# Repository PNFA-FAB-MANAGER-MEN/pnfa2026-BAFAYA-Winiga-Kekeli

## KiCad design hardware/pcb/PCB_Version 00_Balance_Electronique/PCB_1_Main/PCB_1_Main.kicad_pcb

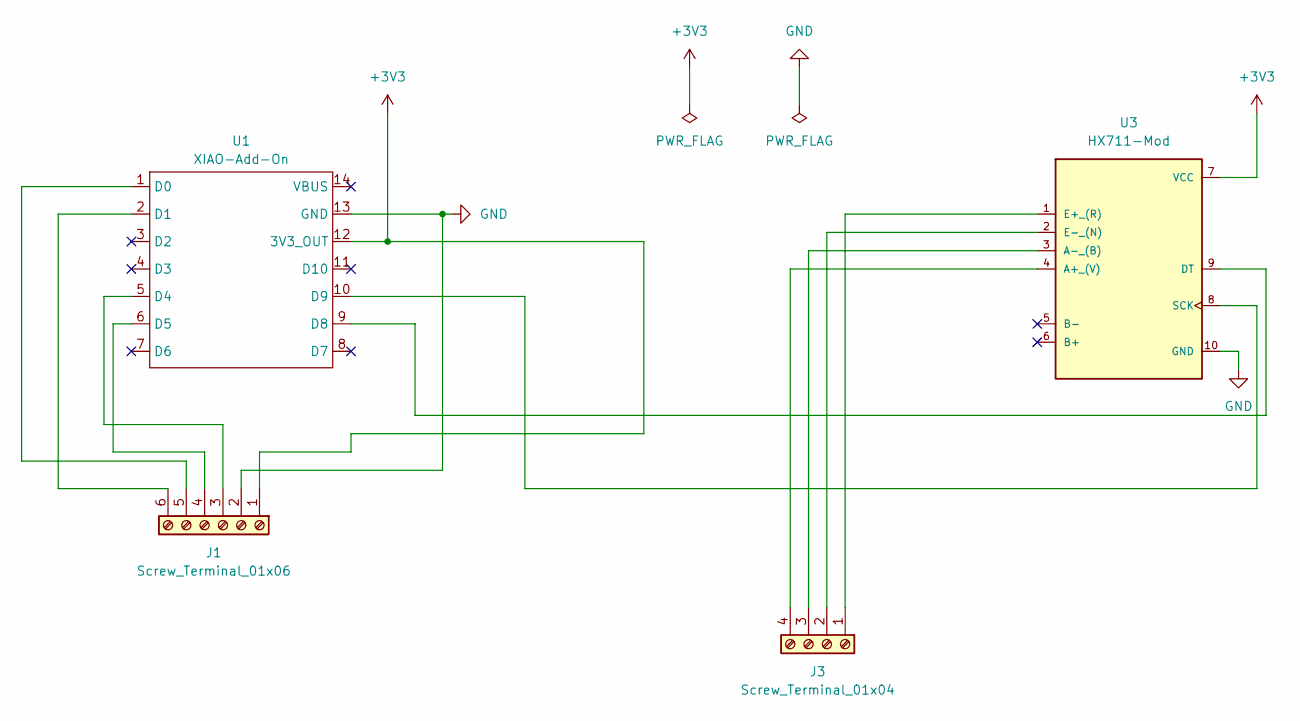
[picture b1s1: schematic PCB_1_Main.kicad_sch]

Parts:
J1: Screw_Terminal_01x06; TerminalBlock_MaiXu_MX126-5.0-06P_1x06_P5.00mm
J3: Screw_Terminal_01x04; TerminalBlock_MaiXu_MX126-5.0-04P_1x04_P5.00mm
U1: XIAO-Add-On; XIAO-14P-Add-On
U3: HX711-Mod; HX711_module

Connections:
+3V3: J1.1, U1.12 (3V3_OUT), U3.7 (VCC)
GND: J1.2, U1.13 (GND), U3.10 (GND)
unnamed: J1.3, U1.5 (D4)
unnamed: J1.4, U1.6 (D5)
unnamed: J1.5, U1.1 (D0)
unnamed: J1.6, U1.2 (D1)
unnamed: J3.1, U3.1 (E+_(R))
unnamed: J3.2, U3.2 (E-_(N))
unnamed: J3.3, U3.3 (A-_(B))
unnamed: J3.4, U3.4 (A+_(V))
unnamed: U1.9 (D8), U3.9 (DT)
unnamed: U1.10 (D9), U3.8 (SCK)

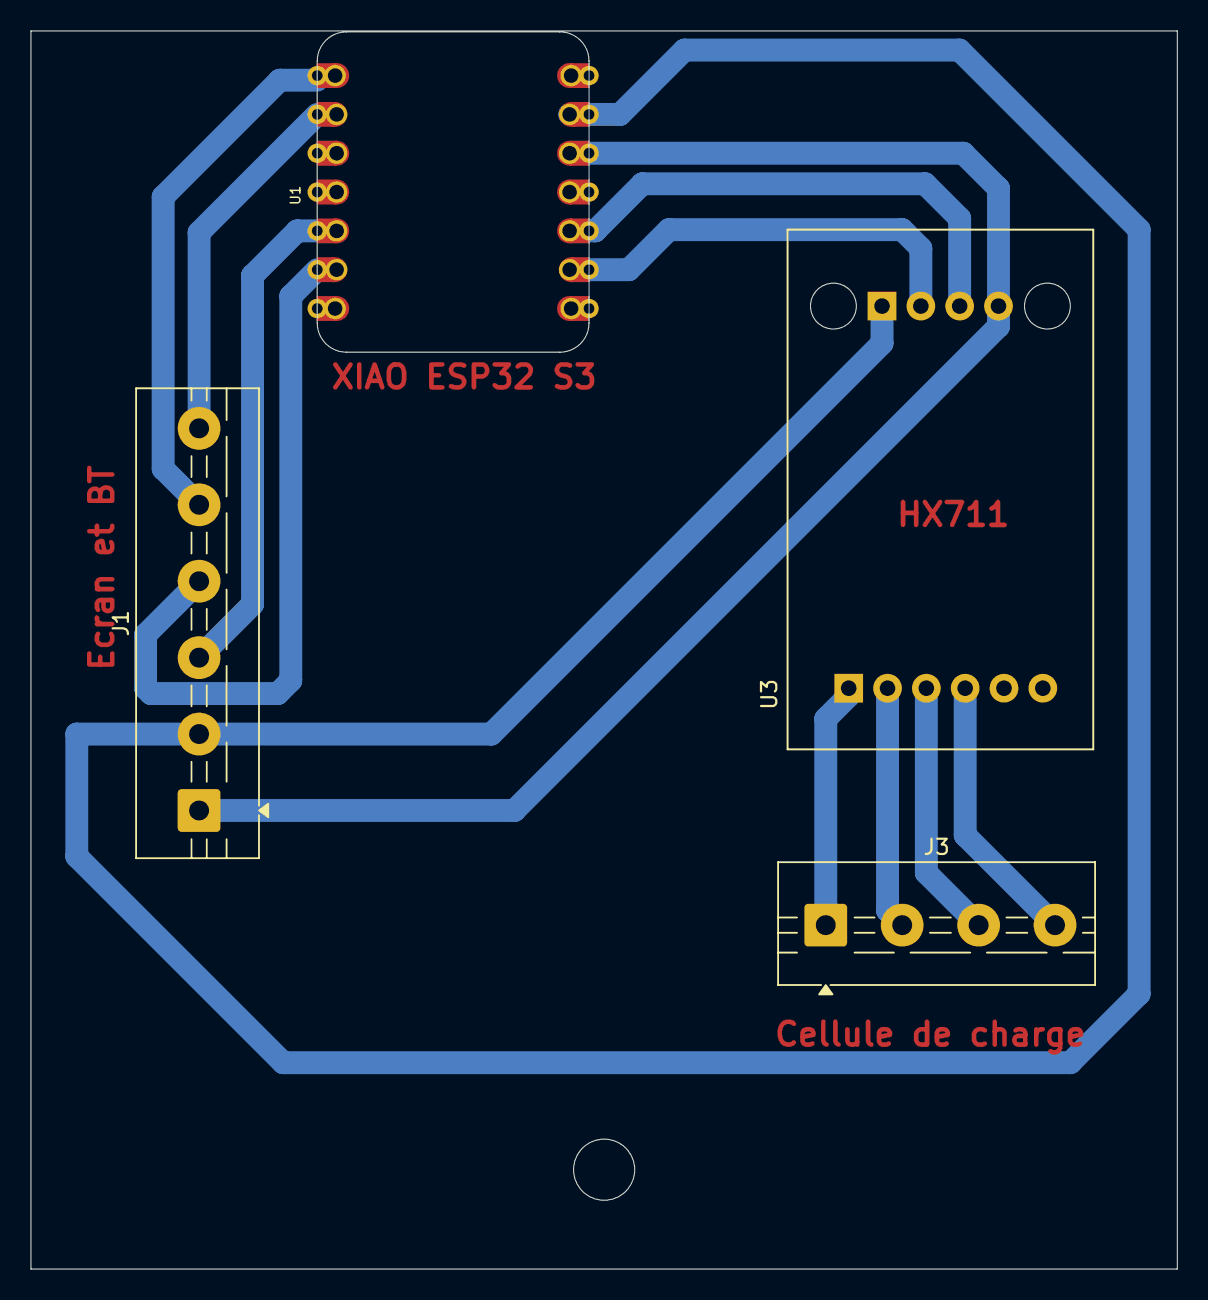
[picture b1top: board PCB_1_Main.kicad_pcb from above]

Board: 2 copper layers, 75.0 x 81.0 mm, 4 parts (0 on the bottom side), 12 nets.

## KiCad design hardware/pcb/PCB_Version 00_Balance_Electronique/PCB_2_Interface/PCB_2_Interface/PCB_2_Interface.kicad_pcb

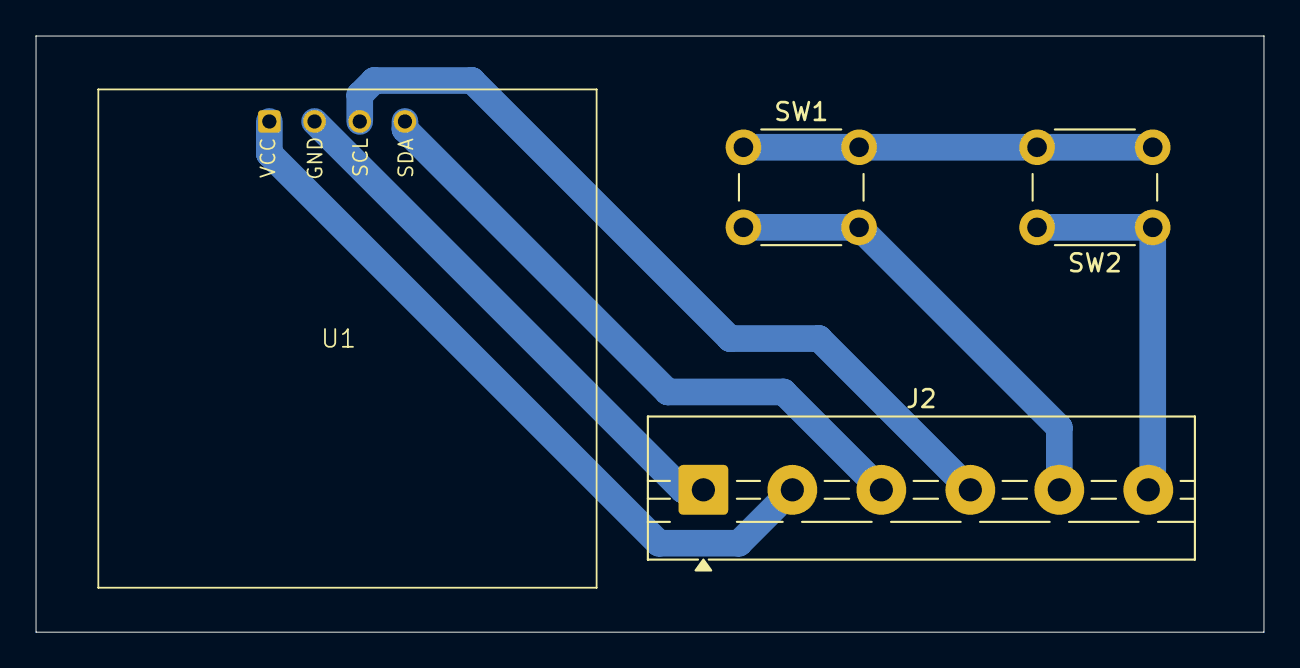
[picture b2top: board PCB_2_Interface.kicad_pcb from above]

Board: 2 copper layers, 69.0 x 33.5 mm, 4 parts (0 on the bottom side), 7 nets.

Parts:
J2: Screw_Terminal_01x06; TerminalBlock_MaiXu_MX126-5.0-06P_1x06_P5.00mm
SW1, SW2: SW_Push; SW_PUSH_6mm
U1: Sans titre

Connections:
+3V3: J2.1, U1.2 (VCC)
GND: J2.2, U1.1 (GND)
unnamed: J2.3, U1.4 (SDA)
unnamed: J2.4, U1.3 (SCL)
unnamed: J2.5, SW1.2
unnamed: J2.6, SW2.1
unnamed: SW1.1, SW2.2
